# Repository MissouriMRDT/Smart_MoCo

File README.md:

# Smart_MoCo_Hardware

Motor controller breakout with VNH ICs, a microcontroller, and CANbus. 
Transmits encoder, limit switch, and motor controller data over CAN.

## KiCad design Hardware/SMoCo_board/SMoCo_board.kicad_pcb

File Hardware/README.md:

# CoreBoard_Hardware
Combines DriveBoard, Multimedia Board, and Gimbal Board functionality into one PCB

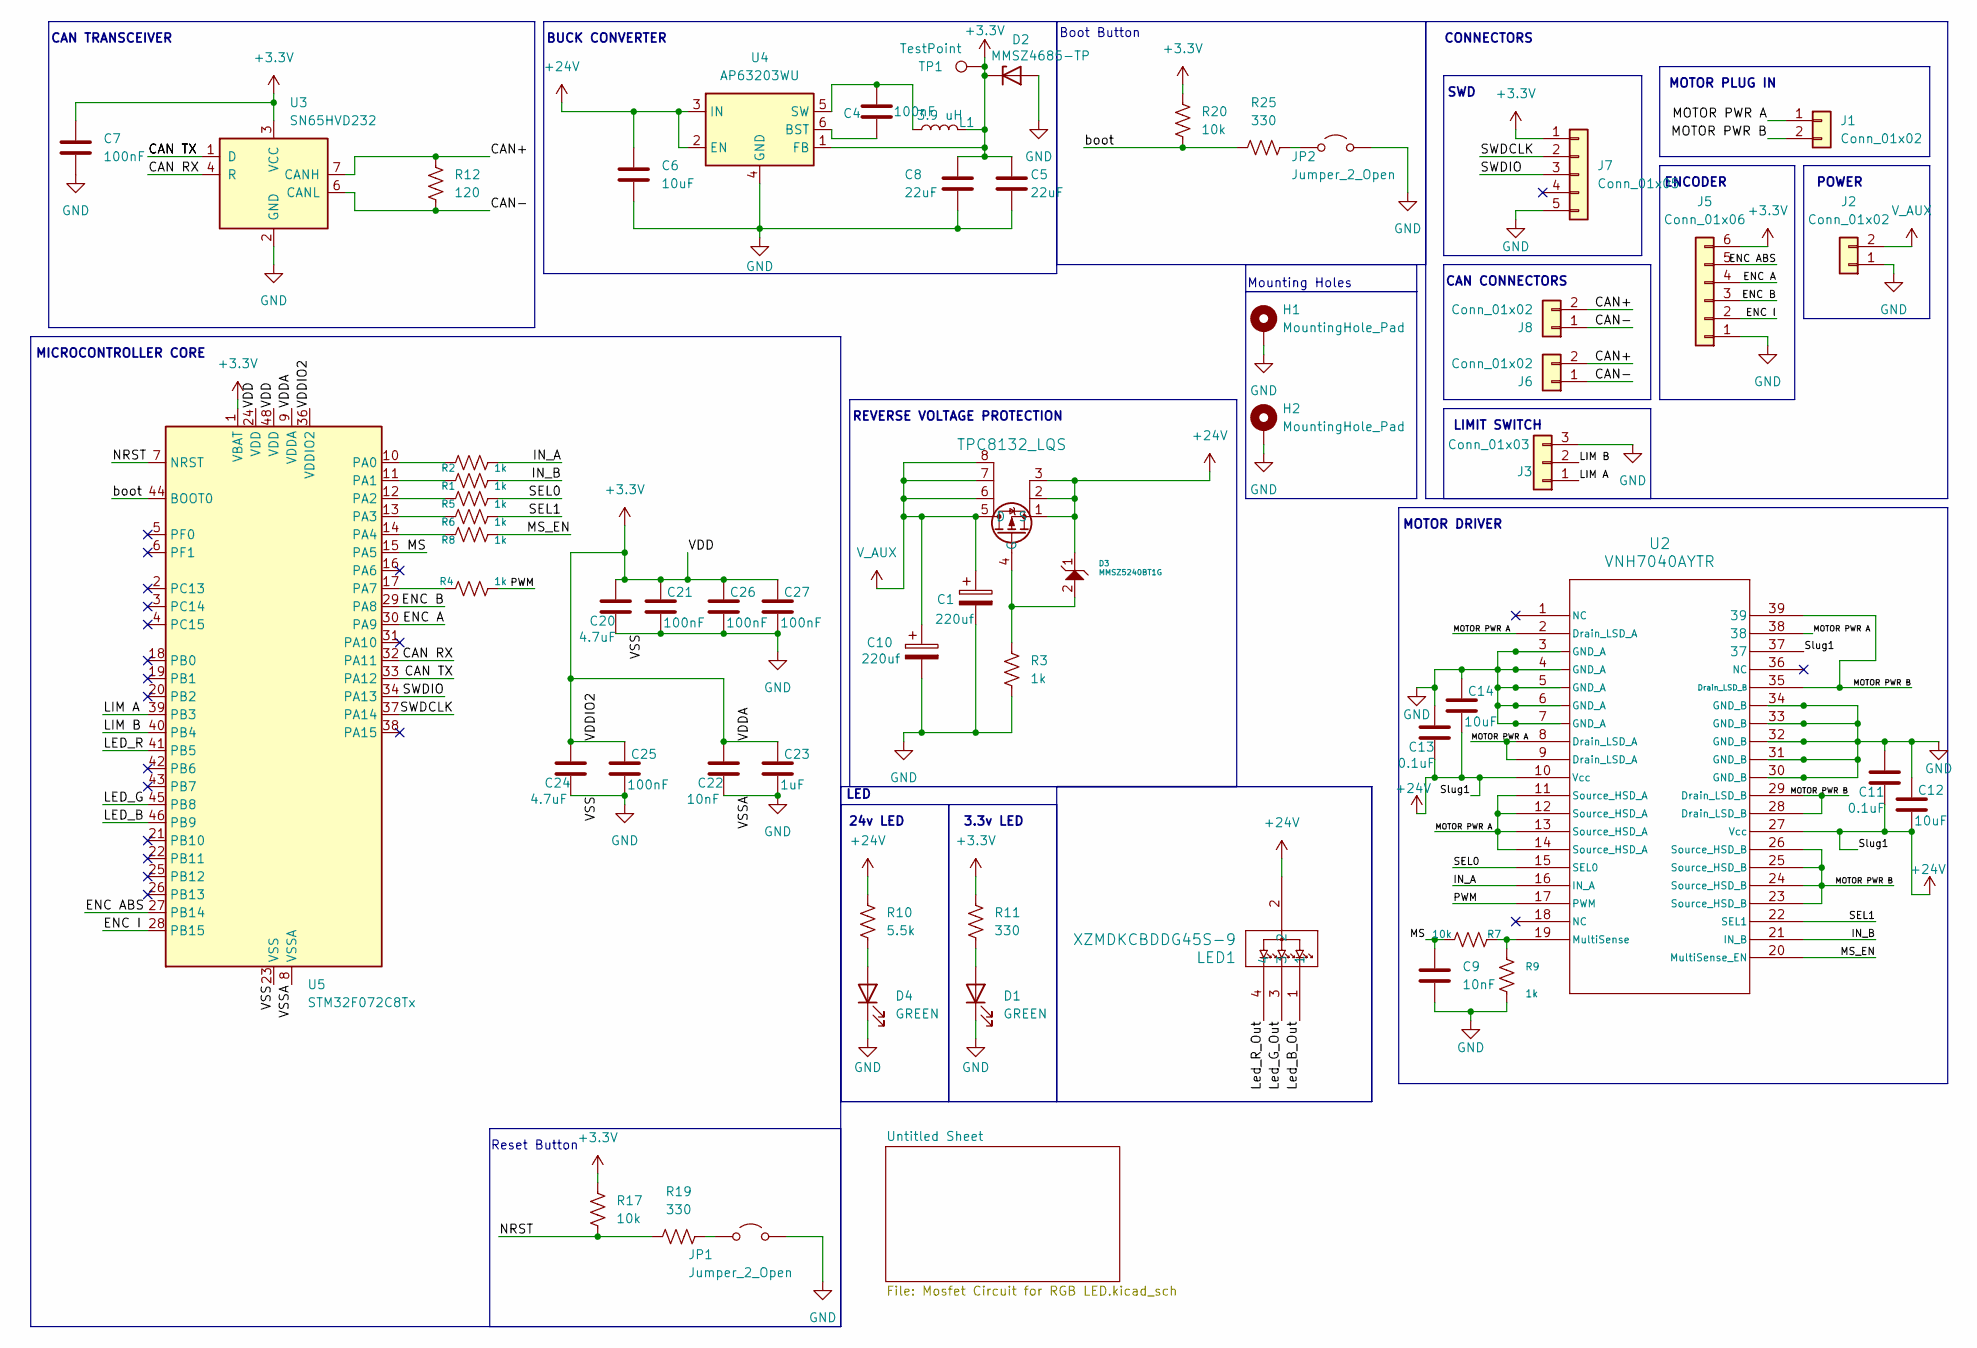
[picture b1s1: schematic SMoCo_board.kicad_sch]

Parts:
C1, C10: 220uf; CP_Radial_D8.0mm_P3.50mm
C4, C7, C21, C25, C26, C27: 100nF; C_0603_1608Metric_Pad1.08x0.95mm_HandSolder
C5, C8: 22uF; C_0603_1608Metric_Pad1.08x0.95mm_HandSolder
C6, C12, C14: 10uF; C_0603_1608Metric_Pad1.08x0.95mm_HandSolder
C9, C22: 10nF; C_0603_1608Metric_Pad1.08x0.95mm_HandSolder
C11, C13: 0.1uF; C_0603_1608Metric_Pad1.08x0.95mm_HandSolder
C20, C24: 4.7uF; C_0603_1608Metric_Pad1.08x0.95mm_HandSolder
C23: 1uF; C_0603_1608Metric_Pad1.08x0.95mm_HandSolder
D1, D4: GREEN; LED_0603_1608Metric
D2: MMSZ4685-TP; D_SOD-523
D3: MMSZ5240BT1G; D_SOD-123
H1, H2: MountingHole_Pad; MountingHole_3.2mm_M3_Pad
J1, J2: Conn_01x02; SolderWire-1.5sqmm_1x02_P6mm_D1.7mm_OD3mm
J3: Conn_01x03; SolderWire-0.5sqmm_1x03_P4.6mm_D0.9mm_OD2.1mm
J5: Conn_01x06; SolderWire-0.5sqmm_1x06_P4.6mm_D0.9mm_OD2.1mm
J6, J8: Conn_01x02; SolderWire-0.5sqmm_1x02_P4.6mm_D0.9mm_OD2.1mm
J7: Conn_01x05; Tag-Connect_TC2030-IDC-FP_2x03_P1.27mm_Vertical
JP1, JP2: Jumper_2_Open; SolderJumper-2_P1.3mm_Open_Pad1.0x1.5mm
L1: 3.9 uH; IND_TFM252012ALMA1R0MTAA_TDK
LED1: XZMDKCBDDG45S-9; PLCC4_SMD-LED_3p2X2p8_SLD
MOSFET1: TPC8132_LQS; SOIC-8_3.9x4.9mm_P1.27mm
R1, R2, R3, R4, R5, R6, R8, R9: 1k; R_0603_1608Metric_Pad0.98x0.95mm_HandSolder
R7, R17, R20: 10k; R_0603_1608Metric_Pad0.98x0.95mm_HandSolder
R10: 5.5k; R_0603_1608Metric_Pad0.98x0.95mm_HandSolder
R11, R19, R25: 330; R_0603_1608Metric_Pad0.98x0.95mm_HandSolder
R12: 120; R_0603_1608Metric_Pad0.98x0.95mm_HandSolder
TP1: TestPoint; TestPoint_Pad_D1.5mm
U2: VNH7040AYTR; POWERSSO-36TP_STM
U3: SN65HVD232; SOIC-8_3.9x4.9mm_P1.27mm
U4: AP63203WU; TSOT-23-6
U5: STM32F072C8Tx; LQFP-48_7x7mm_P0.5mm

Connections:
+3.3V: C5.1, C7.1, C8.1, C20.1, C21.1, C22.1, C23.1, C24.1, C25.1, C26.1, C27.1, D2.1 (K), J5.6, J7.1, L1.2, R11.1, R17.1, R20.1, TP1.1 (1_1), U3.3 (VCC), U4.1 (FB), U5.1 (VBAT), U5.9 (VDDA), U5.24 (VDD), U5.36 (VDDIO2), U5.48 (VDD)
+24V: C6.1, C11.2, C12.2, C13.2, C14.2, D3.1, LED1.2, MOSFET1.1 (S), MOSFET1.2, MOSFET1.3, R10.1, U2.10 (Vcc), U2.27 (Vcc), U2.37, U4.2 (EN), U4.3 (IN)
/CAN RX: U3.4 (R), U5.32 (PA11)
/CAN TX: U3.1 (D), U5.33 (PA12)
/CAN+: J6.2, J8.2, R12.1, U3.7 (CANH)
/CAN-: J6.1, J8.1, R12.2, U3.6 (CANL)
/ENC A: J5.4, U5.30 (PA9)
/ENC ABS: J5.5, U5.27 (PB14)
/ENC B: J5.3, U5.29 (PA8)
/ENC I: J5.2, U5.28 (PB15)
/IN_A: R2.1, U2.16 (IN_A)
/IN_B: R1.1, U2.21 (IN_B)
/LED_B: U5.46 (PB9)
/LED_G: U5.45 (PB8)
/LED_R: U5.41 (PB5)
/LIM A: J3.1, U5.39 (PB3)
/LIM B: J3.2, U5.40 (PB4)
/MOTOR PWR A: J1.1, U2.2 (Drain_LSD_A), U2.8 (Drain_LSD_A), U2.9 (Drain_LSD_A), U2.11 (Source_HSD_A), U2.12 (Source_HSD_A), U2.13 (Source_HSD_A), U2.14 (Source_HSD_A), U2.38
/MOTOR PWR B: J1.2, U2.23 (Source_HSD_B), U2.24 (Source_HSD_B), U2.25 (Source_HSD_B), U2.26 (Source_HSD_B), U2.28 (Drain_LSD_B), U2.29 (Drain_LSD_B), U2.35 (Drain_LSD_B), U2.39
/MS: C9.1, R7.1, U5.15 (PA5)
/MS_EN: R8.1, U2.20 (MultiSense_EN)
/NRST: R17.2, R19.1, U5.7 (NRST)
/PWM: R4.1, U2.17 (PWM)
/SEL0: R5.1, U2.15 (SEL0)
/SEL1: R6.1, U2.22 (SEL1)
/SWDCLK: J7.2, U5.37 (PA14)
/SWDIO: J7.3, U5.34 (PA13)
/boot: R20.2, R25.1, U5.44 (BOOT0)
GND: C1.2, C5.2, C6.2, C7.2, C8.2, C9.2, C10.2, C11.1, C12.1, C13.1, C14.1, C20.2, C21.2, C22.2, C23.2, C24.2, C25.2, C26.2, C27.2, D1.1 (K), D2.2 (A), D4.1 (K), H1.1 (1_1), H2.1 (1_1), J2.1, J3.3, J5.1, J7.4, J7.5, JP1.2 (B), JP2.2 (B), R3.2, R9.2, U2.3 (GND_A), U2.4 (GND_A), U2.5 (GND_A), U2.6 (GND_A), U2.7 (GND_A), U2.30 (GND_B), U2.31 (GND_B), U2.32 (GND_B), U2.33 (GND_B), U2.34 (GND_B), U3.2 (GND), U4.4 (GND), U5.8 (VSSA), U5.23 (VSS), U5.35 (VSS), U5.47 (VSS); also elsewhere on the board
unnamed: D1.2 (A), R11.2
unnamed: D4.2 (A), R10.2
unnamed: JP1.1 (A), R19.2
unnamed: JP2.1 (A), R25.2
unnamed: D3.2, MOSFET1.4 (G), R3.1
unnamed: R7.2, R9.1, U2.19 (MultiSense)
unnamed: C4.1, U4.6 (BST)
unnamed: C4.2, L1.1, U4.5 (SW)
unnamed: R2.2, U5.10 (PA0)
unnamed: R1.2, U5.11 (PA1)
unnamed: R5.2, U5.12 (PA2)
unnamed: R6.2, U5.13 (PA3)
unnamed: R8.2, U5.14 (PA4)
unnamed: R4.2, U5.17 (PA7)
V_AUX: C1.1, C10.1, J2.2, MOSFET1.5 (D), MOSFET1.6, MOSFET1.7, MOSFET1.8

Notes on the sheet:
24v LED
REVERSE VOLTAGE PROTECTION
CONNECTORS
Boot Button
Mounting Holes
MOTOR PLUG IN
ENCODER
BUCK CONVERTER
SWD
Reset Button
LIMIT SWITCH
CAN CONNECTORS
MOTOR DRIVER
MICROCONTROLLER CORE
3.3v LED
CAN TRANSCEIVER
POWER
LED

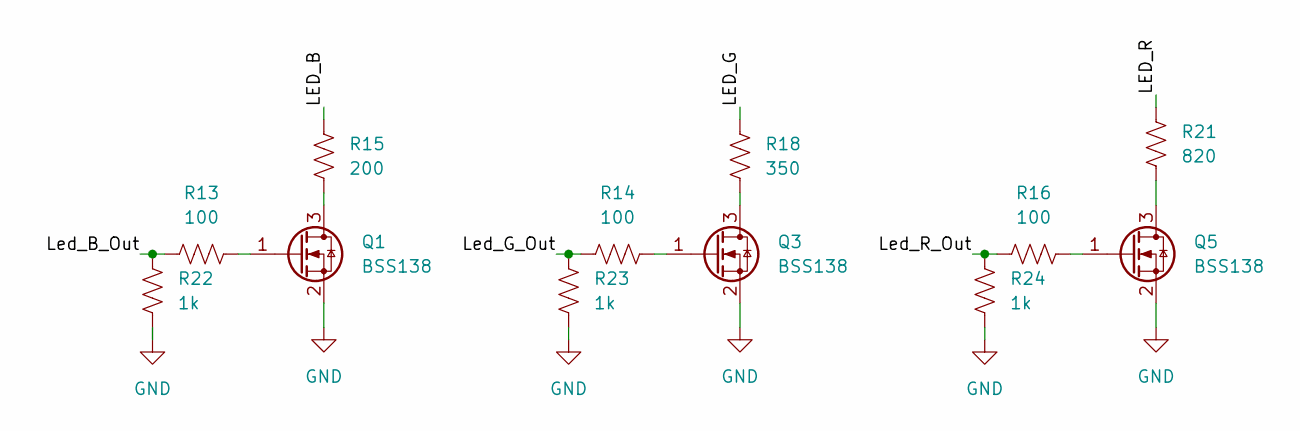
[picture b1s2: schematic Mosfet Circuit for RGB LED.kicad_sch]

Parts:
Q1, Q3, Q5: BSS138; SOT-23
R13, R14, R16: 100; R_0603_1608Metric_Pad0.98x0.95mm_HandSolder
R15: 200; R_0603_1608Metric_Pad0.98x0.95mm_HandSolder
R18: 350; R_0603_1608Metric_Pad0.98x0.95mm_HandSolder
R21: 820; R_0603_1608Metric_Pad0.98x0.95mm_HandSolder
R22, R23, R24: 1k; R_0603_1608Metric_Pad0.98x0.95mm_HandSolder

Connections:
/Untitled Sheet/LED_B: R15.1
/Untitled Sheet/LED_G: R18.1
/Untitled Sheet/LED_R: R21.1
/Untitled Sheet/Led_B_Out: R13.1, R22.1
/Untitled Sheet/Led_G_Out: R14.1, R23.1
/Untitled Sheet/Led_R_Out: R16.1, R24.1
GND: Q1.2 (S), Q3.2 (S), Q5.2 (S), R22.2, R23.2, R24.2; also elsewhere on the board
unnamed: Q1.3 (D), R15.2
unnamed: Q1.1 (G), R13.2
unnamed: Q3.3 (D), R18.2
unnamed: Q3.1 (G), R14.2
unnamed: Q5.3 (D), R21.2
unnamed: Q5.1 (G), R16.2

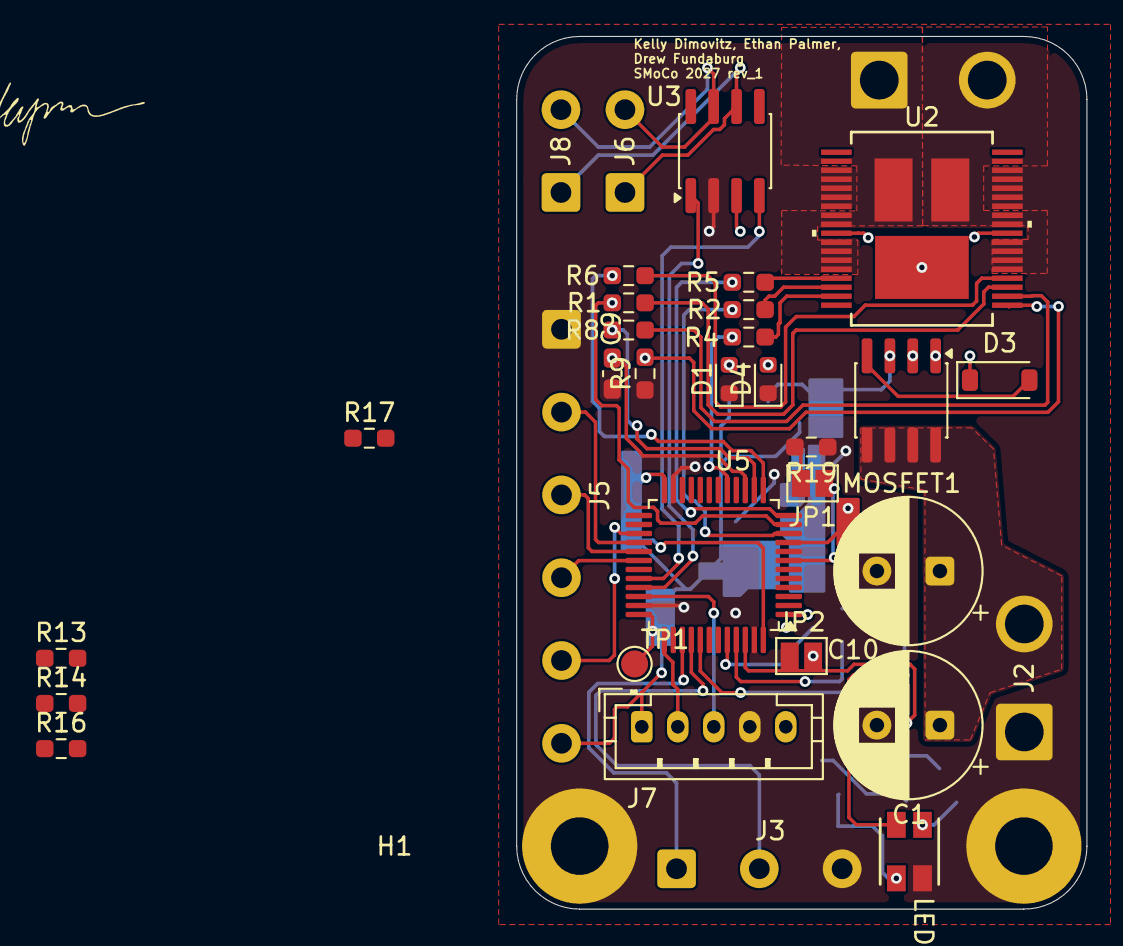
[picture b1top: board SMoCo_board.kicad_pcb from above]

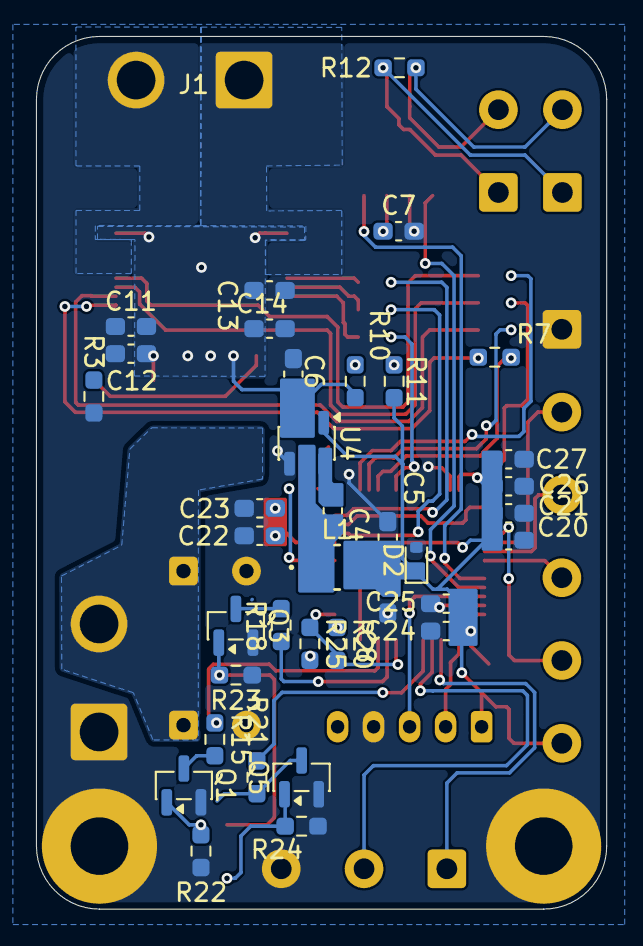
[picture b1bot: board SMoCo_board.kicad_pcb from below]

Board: 4 copper layers, 31.7 x 48.5 mm, 71 parts (37 on the bottom side), 50 nets.

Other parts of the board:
LED: XZM2CRKM2DGFBB45SCCB; PLCC4_3p5x2p8_SLD

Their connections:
GND: LED.4; also elsewhere on the board

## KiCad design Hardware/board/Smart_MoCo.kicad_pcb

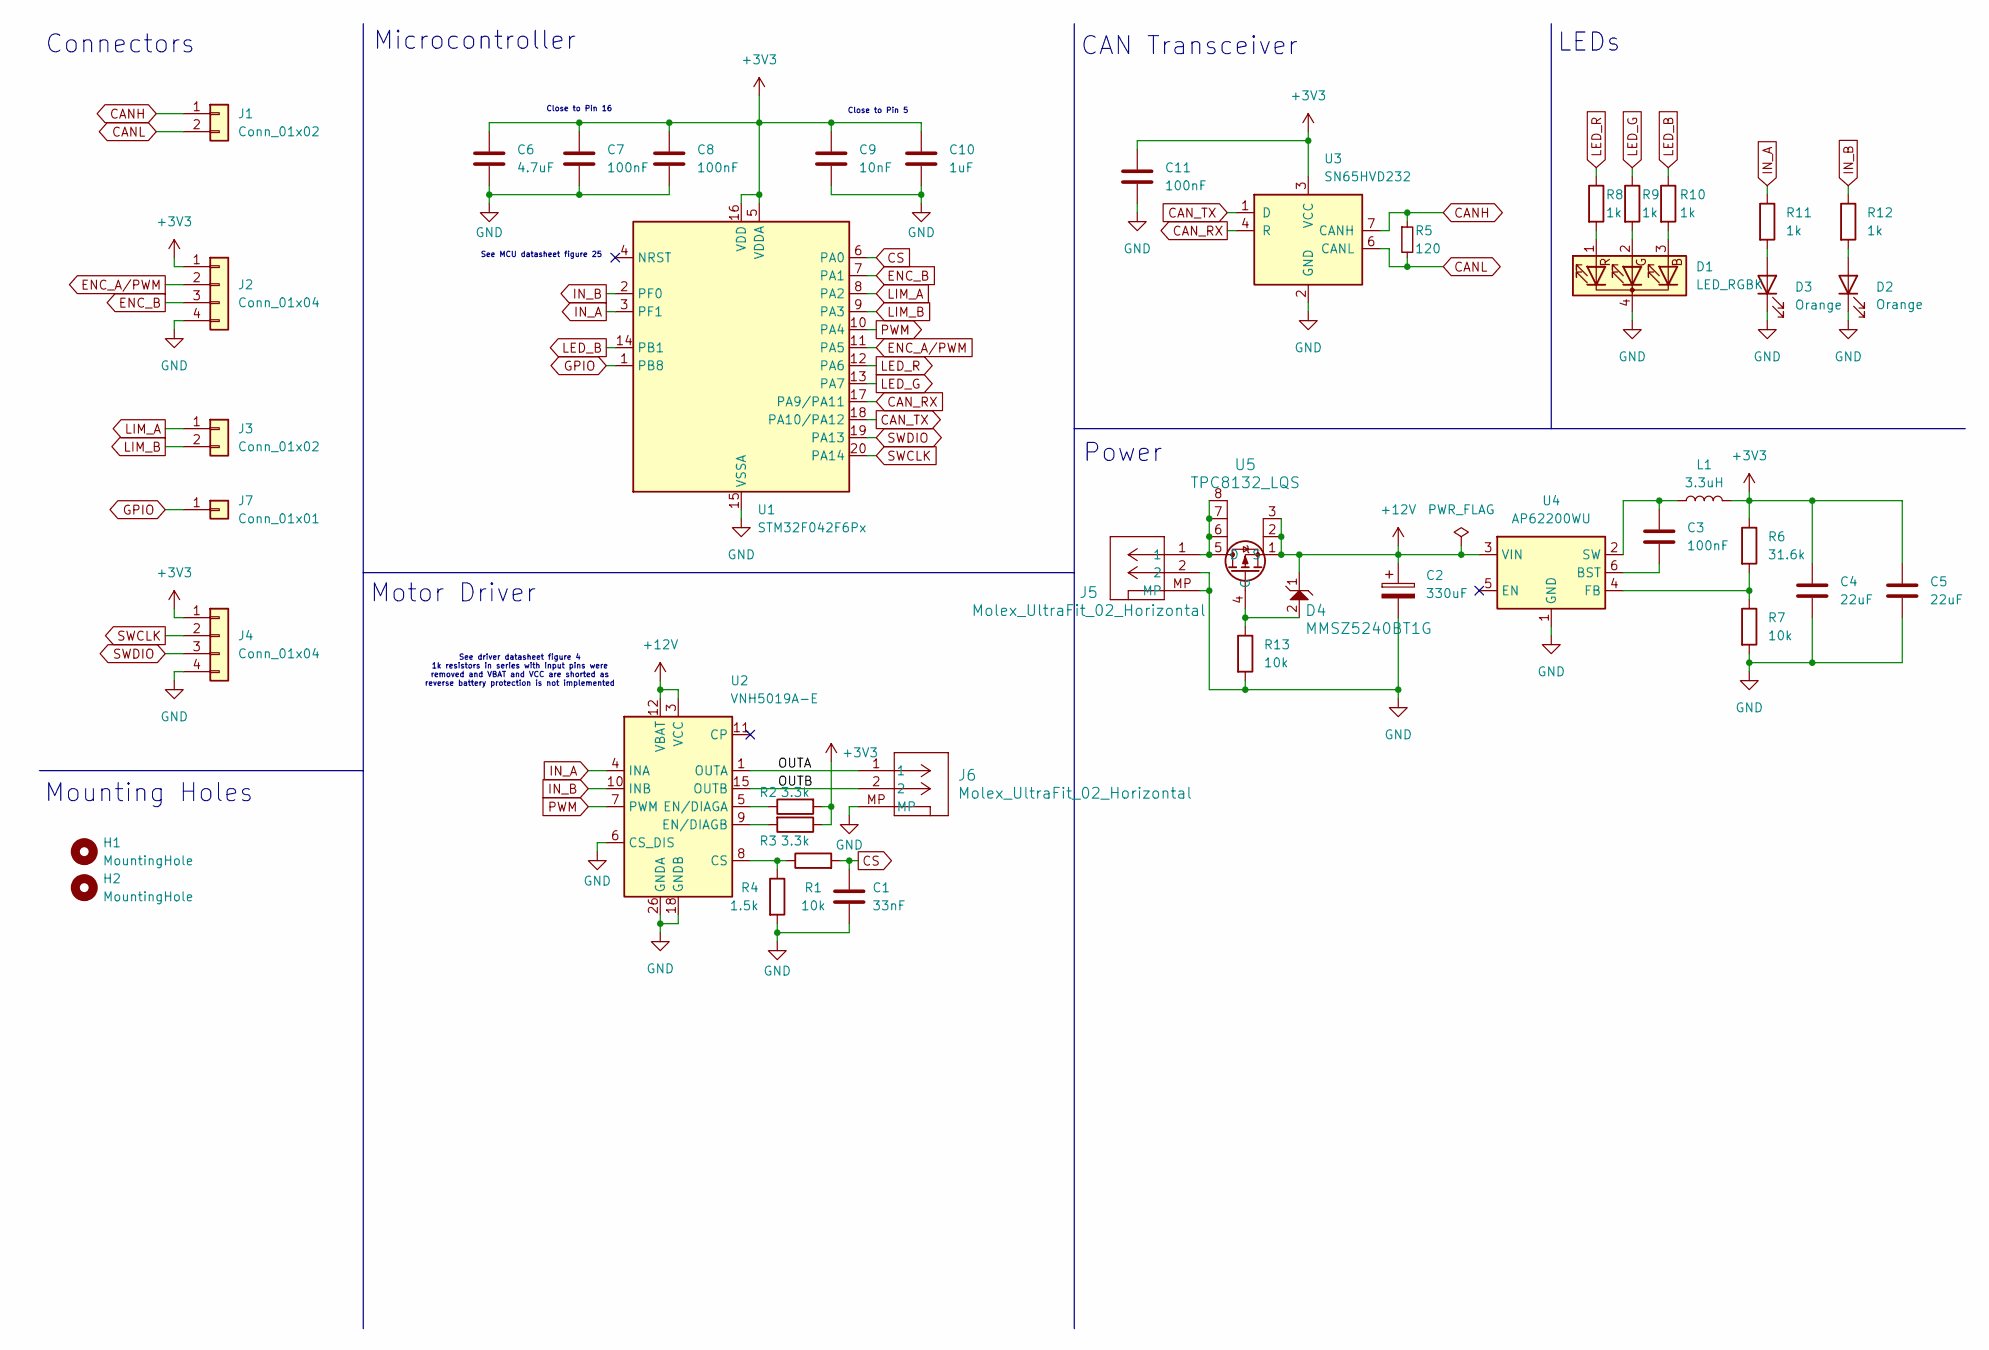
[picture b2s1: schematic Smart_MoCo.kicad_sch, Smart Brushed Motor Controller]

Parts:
C1: 33nF; C_0603_1608Metric_Pad1.08x0.95mm_HandSolder
C2: 330uF; C_Radial_D8.0mm_H11.5mm_P3.50mm
C3, C11: 100nF; C_0603_1608Metric_Pad1.08x0.95mm_HandSolder
C4, C5: 22uF; C_0603_1608Metric_Pad1.08x0.95mm_HandSolder
C6: 4.7uF; C_0402_1005Metric_Pad0.74x0.62mm_HandSolder
C7, C8: 100nF; C_0402_1005Metric_Pad0.74x0.62mm_HandSolder
C9: 10nF; C_0402_1005Metric_Pad0.74x0.62mm_HandSolder
C10: 1uF; C_0402_1005Metric_Pad0.74x0.62mm_HandSolder
D1: LED_RGBK; PLCC4_3p5x2p8_SLD-L
D2, D3: Orange; LED_0603_1608Metric_Pad1.05x0.95mm_HandSolder
D4: MMSZ5240BT1G; SOD-123_ONS-L
H1, H2: MountingHole; Minimal_4_40_Hole
J1, J3: Conn_01x02; JST_XH_S2B-XH-A_1x02_P2.50mm_Horizontal
J2: Conn_01x04; JST_XH_S4B-XH-A_1x04_P2.50mm_Horizontal
J4: Conn_01x04; PinSocket_1x04_P2.54mm_Vertical
J5, J6: Molex_UltraFit_02_Horizontal; MOLEX_UltraFit_02_Horizontal; MPN 1723102000
J7: Conn_01x01; SolderWire-0.5sqmm_1x01_D0.9mm_OD2.1mm
L1: 3.3uH; L_1008_2520Metric_Pad1.43x2.20mm_HandSolder
R1, R7, R13: 10k; R_0603_1608Metric_Pad0.98x0.95mm_HandSolder
R2, R3: 3.3k; R_0603_1608Metric_Pad0.98x0.95mm_HandSolder
R4: 1.5k; R_0603_1608Metric_Pad0.98x0.95mm_HandSolder
R5: 120; R_0603_1608Metric_Pad0.98x0.95mm_HandSolder
R6: 31.6k; R_0603_1608Metric_Pad0.98x0.95mm_HandSolder
R8, R9, R10, R11, R12: 1k; R_0603_1608Metric_Pad0.98x0.95mm_HandSolder
U1: STM32F042F6Px; TSSOP-20_4.4x6.5mm_P0.65mm
U2: VNH5019A-E; ST_MultiPowerSO-30
U3: SN65HVD232; SOIC-8_3.9x4.9mm_P1.27mm
U4: AP62200WU; TSOT-23-6
U5: TPC8132_LQS; SOIC-8_3.9x4.9mm_P1.27mm

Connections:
+3V3: C4.1, C5.1, C6.1, C7.1, C8.1, C9.1, C10.1, C11.1, J2.1, J4.1, L1.2, R2.2, R3.1, R6.1, U1.5 (VDDA), U1.16 (VDD), U3.3 (VCC)
+12V: C2.1, D4.1, U2.3 (VCC), U2.12 (VBAT), U2.13 (VCC), U2.23 (VCC), U2.31 (VCC), U4.3 (VIN), U5.1 (S), U5.2, U5.3
/OUTA: J6.1, U2.1 (OUTA), U2.25 (OUTA), U2.30 (OUTA), U2.33 (OUTA)
/OUTB: J6.2, U2.15 (OUTB), U2.16 (OUTB), U2.21 (OUTB), U2.32 (OUTB)
CANH: J1.1, R5.1, U3.7 (CANH)
CANL: J1.2, R5.2, U3.6 (CANL)
CAN_RX: U1.17 (PA9/PA11), U3.4 (R)
CAN_TX: U1.18 (PA10/PA12), U3.1 (D)
CS: C1.2, R1.2, U1.6 (PA0)
ENC_A/PWM: J2.2, U1.11 (PA5)
ENC_B: J2.3, U1.7 (PA1)
GND: C1.1, C2.2, C4.2, C5.2, C6.2, C7.2, C8.2, C9.2, C10.2, C11.2, D1.4 (K), D2.1 (K), D3.1 (K), J2.4, J4.4, J5.2, J5.MP, J6.MP, R4.2, R7.2, R13.2, U1.15 (VSSA), U2.6 (CS_DIS), U2.18 (GNDB), U2.19 (GNDB), U2.20 (GNDB), U2.26 (GNDA), U2.27 (GNDA), U2.28 (GNDA), U3.2 (GND), U4.1 (GND)
GPIO: J7.1, U1.1 (PB8)
IN_A: R11.1, U1.3 (PF1), U2.4 (INA)
IN_B: R12.1, U1.2 (PF0), U2.10 (INB)
LED_B: R10.1, U1.14 (PB1)
LED_G: R9.1, U1.13 (PA7)
LED_R: R8.1, U1.12 (PA6)
LIM_A: J3.1, U1.8 (PA2)
LIM_B: J3.2, U1.9 (PA3)
unnamed: D1.3 (BA), R10.2
unnamed: D1.2 (GA), R9.2
unnamed: D1.1 (RA), R8.2
unnamed: D2.2 (A), R12.2
unnamed: D3.2 (A), R11.2
unnamed: R1.1, R4.1, U2.8 (CS)
unnamed: R2.1, U2.5 (EN/DIAGA)
unnamed: R3.2, U2.9 (EN/DIAGB)
unnamed: C3.2, U4.6 (BST)
unnamed: R6.2, R7.1, U4.4 (FB)
unnamed: C3.1, L1.1, U4.2 (SW)
unnamed: J5.1, U5.5 (D), U5.6, U5.7, U5.8
unnamed: D4.2, R13.1, U5.4 (G)
PWM: U1.10 (PA4), U2.7 (PWM)
SWCLK: J4.2, U1.20 (PA14)
SWDIO: J4.3, U1.19 (PA13)

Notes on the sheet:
See MCU datasheet figure 25
Close to Pin 5
See driver datasheet figure 4 1k resistors in series with input pins were removed and VBAT and VCC are shorted as reverse battery protection is not implemented
Close to Pin 16
Power
Connectors
Motor Driver
CAN Transceiver
Microcontroller
LEDs
Mounting Holes

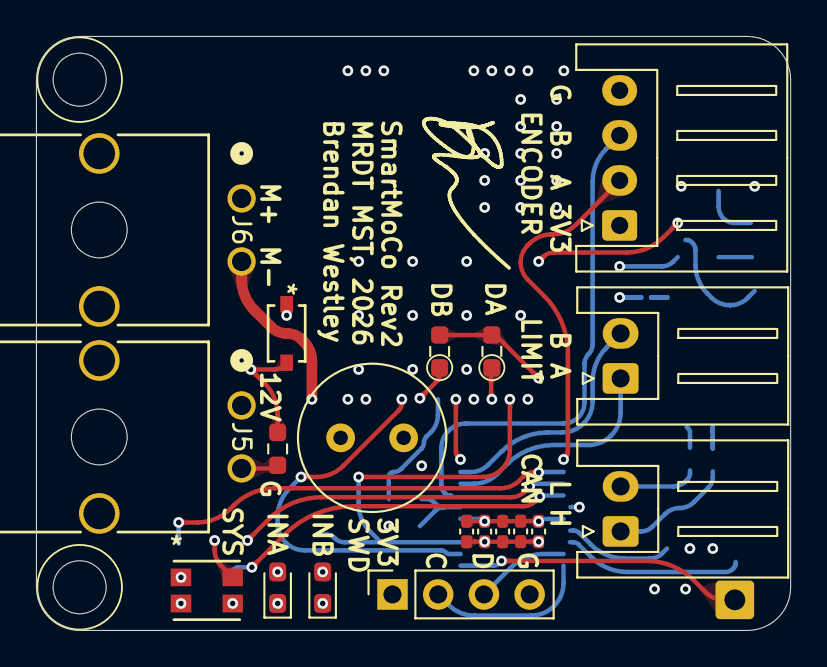
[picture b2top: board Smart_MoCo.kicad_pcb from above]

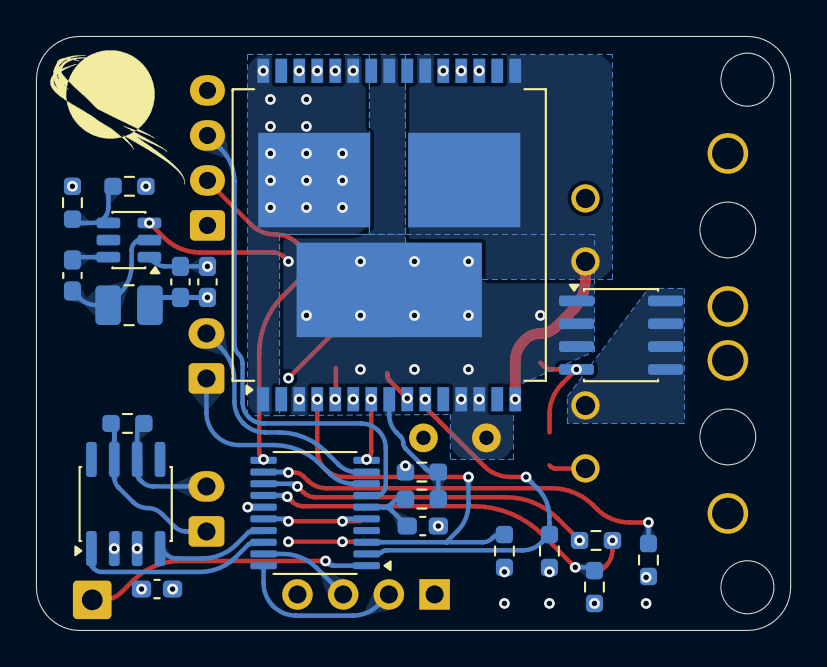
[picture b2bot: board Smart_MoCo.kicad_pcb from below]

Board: 4 copper layers, 41.9 x 33.0 mm, 43 parts (22 on the bottom side), 36 nets.

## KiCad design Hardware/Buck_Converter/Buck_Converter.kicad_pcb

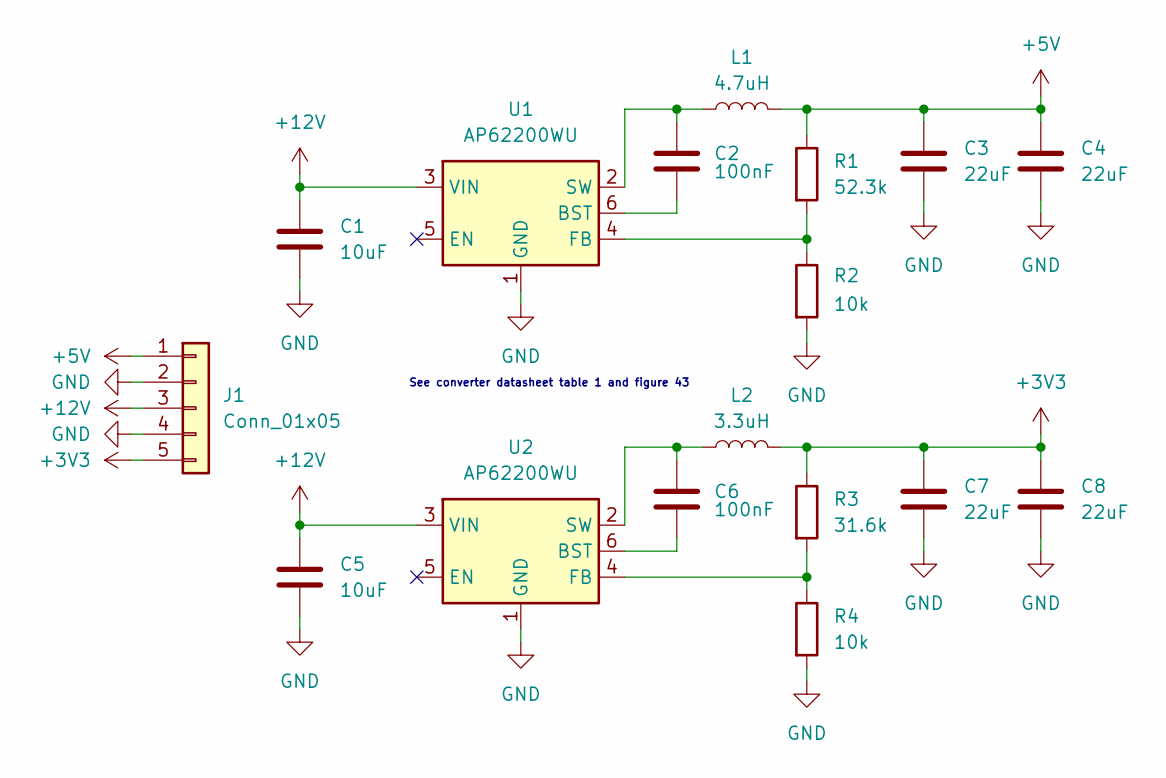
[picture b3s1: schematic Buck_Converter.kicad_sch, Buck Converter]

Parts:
C1, C5: 10uF; C_0603_1608Metric_Pad1.08x0.95mm_HandSolder
C2, C6: 100nF; C_0603_1608Metric_Pad1.08x0.95mm_HandSolder
C3, C4, C7, C8: 22uF; C_0603_1608Metric_Pad1.08x0.95mm_HandSolder
J1: Conn_01x05; PinHeader_1x05_P2.54mm_Vertical
L1: 4.7uH; L_1008_2520Metric_Pad1.43x2.20mm_HandSolder
L2: 3.3uH; L_1008_2520Metric_Pad1.43x2.20mm_HandSolder
R1: 52.3k; R_0603_1608Metric_Pad0.98x0.95mm_HandSolder
R2, R4: 10k; R_0603_1608Metric_Pad0.98x0.95mm_HandSolder
R3: 31.6k; R_0603_1608Metric_Pad0.98x0.95mm_HandSolder
U1, U2: AP62200WU; TSOT-23-6

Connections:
+3V3: C7.1, C8.1, J1.5, L2.2, R3.1
+5V: C3.1, C4.1, J1.1, L1.2, R1.1
+12V: C1.1, C5.1, J1.3, U1.3 (VIN), U2.3 (VIN)
GND: C1.2, C3.2, C4.2, C5.2, C7.2, C8.2, J1.2, J1.4, R2.2, R4.2, U1.1 (GND), U2.1 (GND)
unnamed: C2.2, U1.6 (BST)
unnamed: R1.2, R2.1, U1.4 (FB)
unnamed: C2.1, L1.1, U1.2 (SW)
unnamed: C6.2, U2.6 (BST)
unnamed: R3.2, R4.1, U2.4 (FB)
unnamed: C6.1, L2.1, U2.2 (SW)

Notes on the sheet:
See converter datasheet table 1 and figure 43

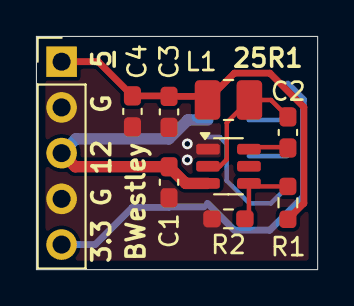
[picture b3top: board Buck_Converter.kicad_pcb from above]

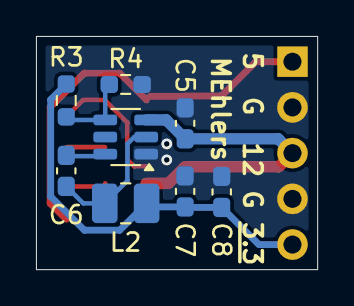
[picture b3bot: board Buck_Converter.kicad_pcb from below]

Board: 2 copper layers, 15.6 x 13.0 mm, 17 parts (8 on the bottom side), 10 nets.

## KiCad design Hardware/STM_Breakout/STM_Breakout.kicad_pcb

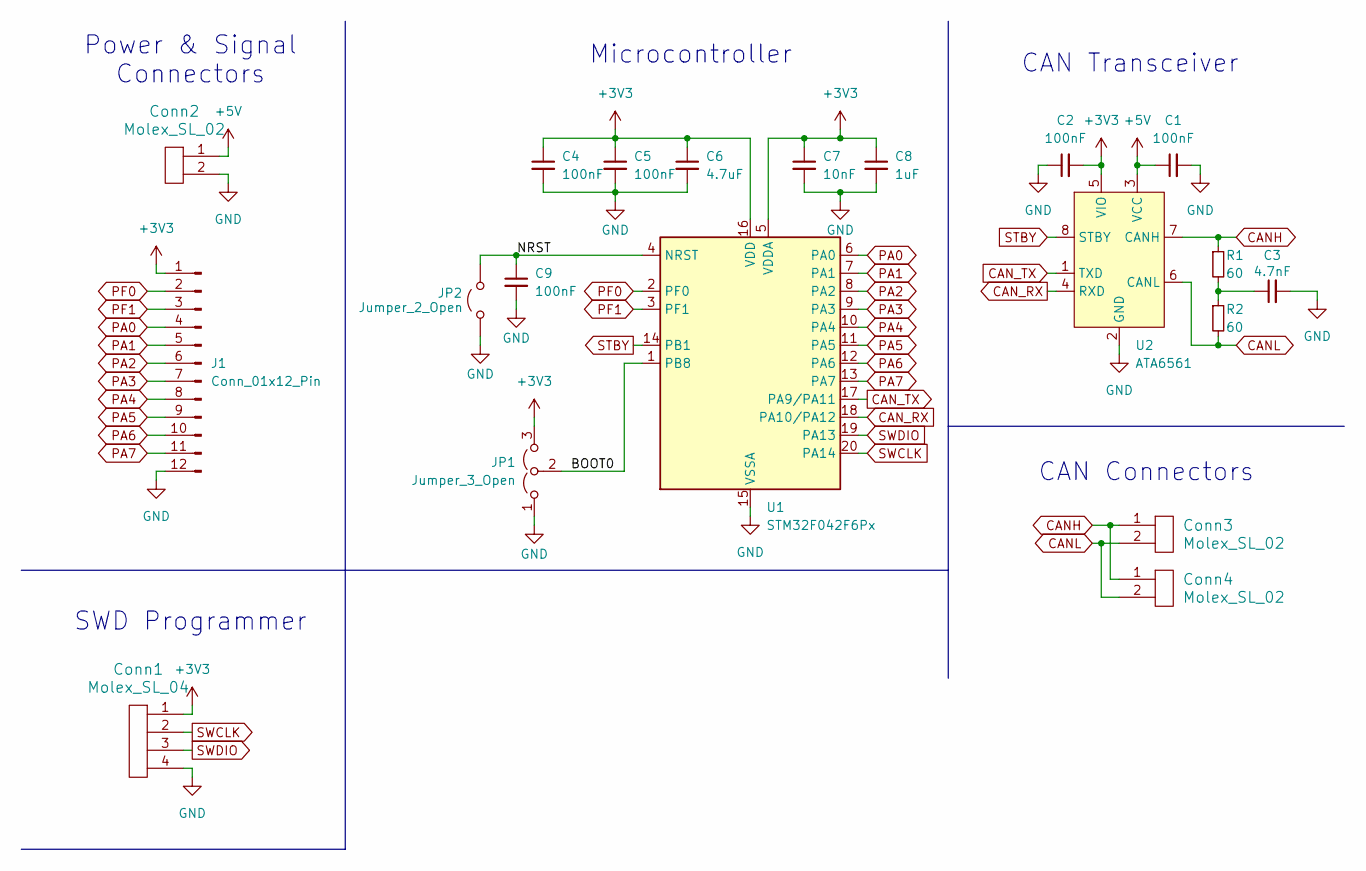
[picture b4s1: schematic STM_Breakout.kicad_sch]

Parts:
C1, C2, C4, C5, C9: 100nF; C_0603_1608Metric_Pad1.08x0.95mm_HandSolder
C3: 4.7nF; C_0603_1608Metric_Pad1.08x0.95mm_HandSolder
C6: 4.7uF; C_0603_1608Metric_Pad1.08x0.95mm_HandSolder
C7: 10nF; C_0603_1608Metric_Pad1.08x0.95mm_HandSolder
C8: 1uF; C_0603_1608Metric_Pad1.08x0.95mm_HandSolder
Conn1: Molex_SL_04; MOLEX_SL_04_Vertical
Conn2, Conn3, Conn4: Molex_SL_02; MOLEX_SL_02_Vertical
J1: Conn_01x12_Pin; PinHeader_2x06_P2.54mm_Vertical
JP1: Jumper_3_Open; PinHeader_1x03_P2.54mm_Vertical
JP2: Jumper_2_Open; PinHeader_1x02_P2.54mm_Vertical
R1, R2: 60; R_0603_1608Metric_Pad0.98x0.95mm_HandSolder
U1: STM32F042F6Px; TSSOP-20_4.4x6.5mm_P0.65mm
U2: ATA6561; SOIC-8_3.9x4.9mm_P1.27mm

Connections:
+3V3: C2.2, C4.1, C5.1, C6.1, C7.1, C8.1, Conn1.1, J1.1, JP1.3 (B), U1.5 (VDDA), U1.16 (VDD), U2.5 (VIO)
+5V: C1.1, Conn2.1, U2.3 (VCC)
/BOOT0: JP1.2 (C), U1.1 (PB8)
/NRST: C9.1, JP2.1 (A), U1.4 (NRST)
CANH: Conn3.1, Conn4.1, R1.1, U2.7 (CANH)
CANL: Conn3.2, Conn4.2, R2.2, U2.6 (CANL)
CAN_RX: U1.18 (PA10/PA12), U2.4 (RXD)
CAN_TX: U1.17 (PA9/PA11), U2.1 (TXD)
GND: C1.2, C2.1, C3.2, C4.2, C5.2, C6.2, C7.2, C8.2, C9.2, Conn1.4, Conn2.2, J1.12, JP1.1 (A), JP2.2 (B), U1.15 (VSSA), U2.2 (GND)
unnamed: C3.1, R1.2, R2.1
PA0: J1.4, U1.6 (PA0)
PA1: J1.5, U1.7 (PA1)
PA2: J1.6, U1.8 (PA2)
PA3: J1.7, U1.9 (PA3)
PA4: J1.8, U1.10 (PA4)
PA5: J1.9, U1.11 (PA5)
PA6: J1.10, U1.12 (PA6)
PA7: J1.11, U1.13 (PA7)
PF0: J1.2, U1.2 (PF0)
PF1: J1.3, U1.3 (PF1)
STBY: U1.14 (PB1), U2.8 (STBY)
SWCLK: Conn1.2, U1.20 (PA14)
SWDIO: Conn1.3, U1.19 (PA13)

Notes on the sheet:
SWD Programmer
Microcontroller
CAN Connectors
CAN Transceiver
Power & Signal Connectors

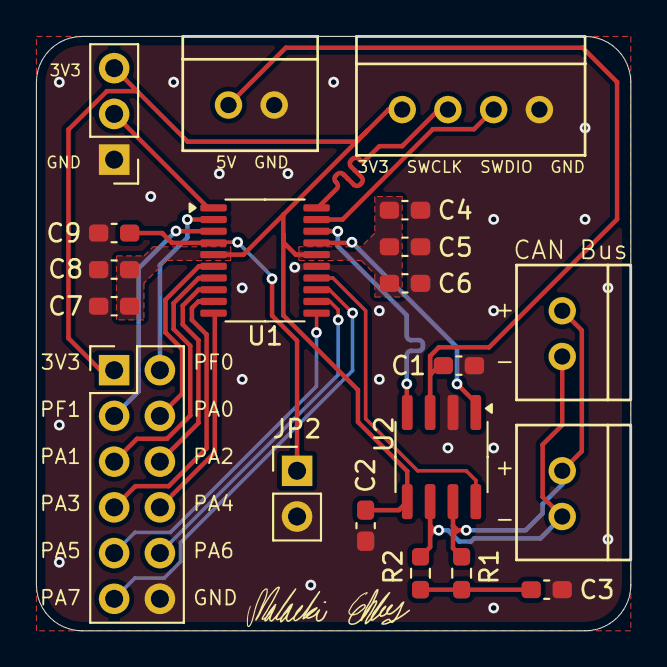
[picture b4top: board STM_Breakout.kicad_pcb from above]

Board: 2 copper layers, 33.0 x 33.0 mm, 20 parts (0 on the bottom side), 23 nets.

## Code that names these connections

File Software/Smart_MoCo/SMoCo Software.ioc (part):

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Mcu.Name=STM32F072C(8-B)Tx
Mcu.Package=LQFP48
Mcu.UserName=STM32F072C8Tx
PA0.GPIOParameters=GPIO_PuPd,GPIO_Label
PA0.GPIO_Label=IN_A
PA0.GPIO_PuPd=GPIO_PULLDOWN
PA0.Signal=GPIO_Output
PA1.GPIOParameters=GPIO_PuPd,GPIO_Label
PA1.GPIO_Label=IN_B
PA1.GPIO_PuPd=GPIO_PULLDOWN
PA1.Signal=GPIO_Output
PA11.Mode=CAN_Activate
PA11.Signal=CAN_RX
PA12.Mode=CAN_Activate
PA12.Signal=CAN_TX
PA13.Mode=Serial_Wire
PA13.Signal=SYS_SWDIO
PA14.Mode=Serial_Wire
PA14.Signal=SYS_SWCLK
PA2.GPIOParameters=GPIO_Label
PA2.GPIO_Label=SEL0
PA2.Signal=GPIO_Output
PA3.GPIOParameters=GPIO_Label
PA3.GPIO_Label=SEL1
PA3.Signal=GPIO_Output
PA4.GPIOParameters=GPIO_PuPd,GPIO_Label
PA4.GPIO_Label=MS_EN
PA4.GPIO_PuPd=GPIO_PULLDOWN
PA4.Signal=GPIO_Output
PA5.GPIOParameters=GPIO_Label
PA5.GPIO_Label=MS_IN
PA5.Mode=IN5
PA5.Signal=ADC_IN5
PA7.GPIOParameters=GPIO_PuPd,GPIO_Label
PA7.GPIO_Label=PWM
PA7.GPIO_PuPd=GPIO_NOPULL
PA7.Signal=S_TIM14_CH1
PA8.GPIOParameters=GPIO_PuPd,GPIO_Label
PA8.GPIO_Label=ENC_B
PA8.GPIO_PuPd=GPIO_NOPULL
PA8.Signal=S_TIM1_CH1
PA9.GPIOParameters=GPIO_PuPd,GPIO_Label
PA9.GPIO_Label=ENC_A
PA9.GPIO_PuPd=GPIO_NOPULL
PA9.Signal=S_TIM1_CH2
PB14.GPIOParameters=GPIO_PuPd,GPIO_Label
PB14.GPIO_Label=ENC_ABS
PB14.GPIO_PuPd=GPIO_NOPULL
PB14.Signal=S_TIM15_CH1
PB15.GPIOParameters=GPIO_PuPd,GPIO_Label
PB15.GPIO_Label=ENC_I
PB15.GPIO_PuPd=GPIO_NOPULL
PB15.Signal=GPXTI15
PB3.GPIOParameters=GPIO_Label
PB3.GPIO_Label=LIM_A
PB3.Signal=GPXTI3
PB4.GPIOParameters=GPIO_Label
PB4.GPIO_Label=LIM_B
PB4.Signal=GPXTI4
PB5.GPIOParameters=GPIO_PuPd,GPIO_Label
PB5.GPIO_Label=LED_R
PB5.GPIO_PuPd=GPIO_NOPULL
PB5.Signal=S_TIM3_CH2
PB8.GPIOParameters=GPIO_PuPd,GPIO_Label
PB8.GPIO_Label=LED_G
PB8.GPIO_PuPd=GPIO_NOPULL
PB8.Signal=S_TIM16_CH1
PB9.GPIOParameters=GPIO_PuPd,GPIO_Label
PB9.GPIO_Label=LED_B
PB9.GPIO_PuPd=GPIO_PULLDOWN
PB9.Signal=S_TIM17_CH1
board=custom

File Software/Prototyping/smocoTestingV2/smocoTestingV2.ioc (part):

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Mcu.Name=STM32F042F6Px
Mcu.Package=TSSOP20
Mcu.UserName=STM32F042F6Px
PA0.GPIOParameters=GPIO_Label
PA0.GPIO_Label=CS
PA0.Mode=IN0
PA0.Signal=ADC_IN0
PA1.GPIOParameters=GPIO_Label
PA1.GPIO_Label=ENC_B
PA1.Signal=S_TIM2_CH2
PA11.GPIOParameters=GPIO_Speed,GPIO_PuPd
PA11.GPIO_PuPd=GPIO_PULLUP
PA11.GPIO_Speed=GPIO_SPEED_FREQ_HIGH
PA11.Mode=CAN_Activate
PA11.Signal=CAN_RX
PA12.GPIOParameters=GPIO_Speed,GPIO_PuPd
PA12.GPIO_PuPd=GPIO_NOPULL
PA12.GPIO_Speed=GPIO_SPEED_FREQ_HIGH
PA12.Mode=CAN_Activate
PA12.Signal=CAN_TX
PA13.Mode=Serial_Wire
PA13.Signal=SYS_SWDIO
PA14.Mode=Serial_Wire
PA14.Signal=SYS_SWCLK
PA2.GPIOParameters=GPIO_PuPd,GPIO_Label,GPIO_ModeDefaultEXTI
PA2.GPIO_Label=LIM_A
PA2.GPIO_ModeDefaultEXTI=GPIO_MODE_IT_FALLING
PA2.GPIO_PuPd=GPIO_PULLUP
PA2.Signal=GPXTI2
PA3.GPIOParameters=GPIO_PuPd,GPIO_Label
PA3.GPIO_Label=LIM_B
PA3.GPIO_PuPd=GPIO_PULLUP
PA3.Signal=GPIO_Input
PA4.GPIOParameters=GPIO_Label
PA4.GPIO_Label=PWM
PA4.Signal=S_TIM14_CH1
PA5.GPIOParameters=GPIO_Label
PA5.GPIO_Label=ENC_A
PA5.Signal=S_TIM2_CH1_ETR
PA6.GPIOParameters=GPIO_Label
PA6.GPIO_Label=LED_R
PA6.Signal=S_TIM3_CH1
PA7.GPIOParameters=GPIO_Label
PA7.GPIO_Label=LED_G
PA7.Signal=S_TIM3_CH2
PB1.GPIOParameters=GPIO_Label
PB1.GPIO_Label=LED_B
PB1.Signal=S_TIM3_CH4
PB8.GPIOParameters=GPIO_Label
PB8.GPIO_Label=GPIO
PB8.Signal=GPIO_Input
PF0-OSC_IN.GPIOParameters=GPIO_Label
PF0-OSC_IN.GPIO_Label=IN_B
PF0-OSC_IN.Signal=GPIO_Output
PF1-OSC_OUT.GPIOParameters=GPIO_Label
PF1-OSC_OUT.GPIO_Label=IN_A
PF1-OSC_OUT.Signal=GPIO_Output
board=custom

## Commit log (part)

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2024-09-07 Added .gitignore
2024-09-23 Added KiCAD files
2024-09-23 Create KiCAD projects for breakout boards
2024-09-26 Create breakout for STM32 and CAN transceiver
2024-09-26 Made buck circuit
2024-09-26 Made buck converter in buck breakout
2024-10-05 Finish STM Breakout Schematic
2024-10-05 Footprint assignments for STM Breakout
2024-10-13 Finish Buck converter schematic and footprint assignments
2024-10-13 Finish buck converter layout
2024-10-13 Generate BOM for buck breakout
2024-10-14 Finish STM32 Breakout Layout
2024-10-14 Generate BOM for STM32 breakout
2024-10-14 Increase header pitch in STM32 breakout
2024-10-16 Add second capacitor to buck breakout output
2024-10-22 Replace reset button with jumper
2024-11-01 Generated gerbs for buck and STM32 breakouts
2024-11-01 Added drill files
2025-03-31 Initial design
2025-04-01 Modify CAN circuit
2025-04-01 Add Buck_Converter daughterboard
2025-04-02 Reviewed
2025-04-03 Implement schematic first review feedback and finish PCB layout
2025-04-03 Add Buck Converter pin labels
2025-04-08 Prepare for board review
2025-04-08 Update LED resistor values
2025-04-09 Implement board review changes
2025-08-27 CAN Testing
2025-10-24 Tested error messages, open loop control
2025-11-01 Change power connectors, increase layer count to 4, and reroute
2025-11-02 Change power connectors again
2025-11-02 Melt traces
2025-11-02 Move mounting hole
2025-11-05 Change signal connectors to horizontal JST SH
2025-11-05 Shrink board to 27x40mm
2025-11-10 Update gerbs and bom
2025-11-10 Update bom
2025-11-11 Add step
2025-11-11 Added bulk capacitors and kicad github action
2025-11-11 Fix spelling error in github action
2025-11-12 Via stitch 12V and OUT planes
2025-11-12 Update via stitching
2025-11-12 Fix vias on edges of pads
2025-11-12 Revert local library paths to be relative to KIPRJMOD
2025-11-12 Rebuild fills and update step
2025-12-10 Added absolute and quadurature encoder support
2025-12-10 Reorganize Hardware folder and remove unused boards
2025-12-16 Correct silkscreen labels
2025-12-23 Correct tick timer
2025-12-23 Add CAN_UI and debug telemetry
2026-01-30 Rename angle to position
2026-02-04 Add filtering to ignore ext ids
2026-02-05 Use trapezoid in open loop
2026-02-05 Add CAN parameters to README.md
2026-03-15 Redesign hardware
2026-03-15 Incorporate review 1 feedback
2026-03-16 Incorporate review 2 feedback
2026-03-23 Final design files as ordered
2026-03-23 Change CAN packet description and switch from HAL to LL
2026-04-10 Implement working scheduler, CAN, limit switch, encoder, open loop
2026-04-10 Migrate to Rev2 hardware, add RGB, fix calibration, adjust timing
2026-04-12 Send SMOCO_MID_ERROR
2026-04-13 Fix encoder bug and add status LED priority
2026-04-13 Remove obsolete defines
2026-04-18 Switch CAN_UI to use usb serial inerface
2026-04-21 Closed Loop Override and tuned PID
    In progress Closed loop Override
    PID Rough Tuned
2026-04-21 You committed to the wrong repo, bozo
    This reverts commit fa1cbf81540806600e269eb86760297bdc7d91b8.
2026-04-28 Fix encoder rollover bug
2026-05-20 Add LED error codes to README
2026-05-20 Remove color code mistake
